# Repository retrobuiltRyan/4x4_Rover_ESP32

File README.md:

# 4x4_Rover_ESP32
Video is a great overview of capabilites and features.<br>

Generic platform for 1:10 scale robot rover (skid steer style) with ESP32 and PS4 controller.  Hardware [mostly] from scratch. The 1:10 scale (primarily wheel span and chassis width) mimics some common RC and toy-scale bodies. Makes a uniquie sleeper build that can share a body from off-the-shelf kids toys. PCB has enough functionality to expand into complex robots.

PCB can control up to 6 DC motors and 8 Servo Motors. 

## CAD Project (View only) Feel free remix!
[4x4 Rover CAD](https://cad.onshape.com/documents/4f9534eae9bdb33bcf172fe9/w/a4954ea2d6d5d21b33e1d9c4/e/6819e643c891bac21c58d472) (Make a free onShape account to copy and edit)

## 🔩 Mechanical Hardware/Fasteners for Assembly (BoM)
| Item | Assembly     | Description                                | Qty | Cost   | Line Total | Vendor Link / McMaster Part#         |
|------|--------------|--------------------------------------------|-----|--------|------------|--------------------------------------------------------------------------------------|
| 1    | Wheel        | Lego "Compatible" Tire 94x38 (or similar)  | 1   | $17.65 | $17.65     | [Link](https://www.aliexpress.us/item/3256808684598937.html)                         |
| 2    | Drive        | Shaft Coupler, 4mm dia                     | 4   | $1.65  | $6.60      | [Link](https://www.aliexpress.us/item/3256805863207590.html)                         |
| 3    | Drive        | Motor 12V, 82 RPM                          | 4   | $5.74  | $22.96     | [Link](https://www.aliexpress.us/item/3256807500148966.html) or [Link](https://www.aliexpress.us/item/3256807350691232.html)                       |
| alt3 | Drive        | Motor 12V, 82 RPM + RC Wheel               | 4   | $6.46  | $25.84     | [Link](https://www.aliexpress.us/item/3256806026937992.html)                         |
| 5    | Chassis      | #6-32 x 0.5 in Round Head Screw            | 28  | $0.03  | $0.94      | 90279A148                                                                            |
| 6    | Chassis      | #6-32 x 0.75 in Round Head Screw           | 20  | $0.04  | $0.83      | 90279A151                                                                            |
| 7    | Chassis      | #6-32 nut                                  | 20  | $0.02  | $0.40      | 90480A007                                                                            |
| 8    | Chassis      | #6-32 nylon lock nut                       | 20  | $0.04  | $0.80      | 99397A622                                                                            |
| 9    | Chassis      | #6-32 x 1.0 in F/F Hex Standoff (optional) | 4   | $0.47  | $1.88      | 90480A005                                                                            |
| 10   | Wheel        | #4-40 x 0.5 in Round Head Screw            | 16  | $0.02  | $0.32      | 90272A110                                                                            |
| 11   | Wheel        | #4-40 nut                                  | 16  | $0.01  | $0.16      | 90480A005                                                                            |
| 12   | Wheel        | #4-40 lock nut (optional)                  | 16  | $0.03  | $0.48      | 90631A005                                                                            |
| 13   | On/Off switch | Switch, SPST                              | 1   | $0.71  | $0.71      | [Link](https://www.digikey.com/en/products/detail/e-switch/RA11131121/2720267)       |
| 14   | 3D Print Parts| PLA Filament (or whatever)                | ~650g |$0.02/g | $13      | any                                                                                  | 
|      |              |                                            |     |        | **$66.74** | Alternate hardware not included in total cost                                        |

### Optional Forklift Assembly Motors + Parts. *Not a comprehensive list- just the essentials*
| Item | Assembly     | Description                                | Qty | Cost   | Line Total | Vendor Link / McMaster Part#         |
|------|--------------|--------------------------------------------|-----|--------|------------|--------------------------------------------------------------------------------------|
| 15   |Forklift      |Motor High Torque 12V, 50RPM, (37mm dia)    |  1  | $14    | $14        |   [Amazon](https://www.amazon.com/dp/B07K9KPDNV) or [AliExpress](https://www.aliexpress.us/item/2251832401105488.html)     |
|16    |Forklift      | Flange Coupler 6mm                         | 1    |$2     | $2         |  [AliExpress](https://www.aliexpress.us/item/3256805863207590.html?) |
| 17   |Forklift      |Motor (Linear Actuator ) 12V 50mm-stroke 15mm/s 64N        | 2   | $22    | $44        |    [AliExpress](https://www.aliexpress.us/item/3256808499012288.html)                           |
| 18   |Forklift      |Bearing 625ZZ , 16mm OD dia, (5x16x5mm)                    | 8   |$0.55   |$4.40       |[AliExpress](https://www.aliexpress.us/item/3256809469842556.html)                    |
| 19   |Forklift      |Bearing, 11mm OD dia, (5x11x5mm)                           | 10  | $0.25  | $2.50      | [AliExpress](https://www.aliexpress.us/item/3256807482131308.html)                   |                           

## 🪫 Electronics (Control and Drive PCB)
PS4 Controller (Renewed) https://www.amazon.com/dp/B07QD2HK7B/ref=dp_cr_wdg_tit_rfb  (subject to availability most of the time)
| Reference | Value | Qty | DigiKey P/N | Adafruit P/N | AliExpress | Line total Cost |
|------------|--------|-----|--------------|---------------|-------------|-----------------|
| BZ1 | Buzzer_5V | 1 | 445-2525-1-ND |  |  | 0.62 |
| C1,C3,C4,C5,C7,C8,C9 | 0.1uF 50V | 7 | 1276-1068-1-ND |  |  | 0.91 |
| C6,C10,C11 | 0.22uF 50V CER | 3 | 445-2283-1-ND |  |  | 0.78 |
| C12,C13,C14 | 22uF 50V | 3 | 399-11438-1-ND |  |  | 1.05 |
| D1,D5,D10,D11 | LED | 4 | 1080-1419-1-ND |  |  | 0.84 |
| D6,D7,D8,D9 | WS2812B | 4 |  | 3094 |  | 0.64 |
| D12 | SMF15A | 1 | SMF15A-E3-08CT-ND |  |  | 0.13 |
| J1 | PINHD_1x2_Male | 1 | S1012EC-40-ND |  |  | 0.43 |
| J2,J12,J14,J16 | Screw_Terminal_4_P3.50mm | 4 | 732-691243110004-ND |  |  | 8.28 |
| J3,J15 | ServoPort_04 | 2 | S1012EC-40-ND |  |  | 0.86 |
| J4,J5,J8,J13 | Screw_Terminal_2_P3.50mm | 4 | 732-2747-ND |  |  | 3.16 |
| J9 | Barrel_Jack | 1 | EJ508A-ND |  |  | 1.22 |
| J17 | PINHD_1x3_Male | 1 |  |  |  | 0 |
| Q1 | MOSFET P-CH 30V 25A TO252 | 1 | 785-1106-1-ND |  |  | 1.43 |
| Q2 | MMBT2222A | 1 | MMBT2222ATPMSCT-ND |  |  | 0.1 |
| Q3 | AO3400A | 1 | 785-1000-1-ND |  |  | 0.46 |
| R1,R2,R4,R7,R8,R9, R10,R13,R18,R22, R36,R37,R38 | 10K | 12 | 311-10.0KFRCT-ND |  |  | 0.14 |
| R3,R6 | 100 | 2 | 311-100FRCT-ND |  |  | 0.2 |
| R5,R19,R20,R32 | 1K | 4 | 311-1.00KFRCT-ND |  |  | 0.44 |
| R16 | 220 | 1 | 311-220FRCT-ND |  |  | 0.1 |
| R17,R21 | 330 | 2 | 311-330FRCT-ND |  |  | 0.22 |
| R33 | 100k | 1 | 311-100KFRCT-ND |  |  | 0.1 |
| RN1,RN2,RN3 | 220 array | 3 | CAY16-201J4LFCT-ND |  |  | 0.3 |
| U1 | INA260 | 1 | 296-47777-1-ND |  |  | 5.52 |
| U2 | ESP32 | 1 | 1965-ESP32-DEVKITC-32UE-ND |  |  | 10 |
| U3 | PCA9685PW | 1 | 568-11925-1-ND |  |  | 3.04 |
| U4,U6,U9 | DRV8833 | 3 |  |  | [Link](https://www.aliexpress.us/item/3256806096142480.html) | 5.23 |
| U5 | UCC27511ADBV | 1 | 296-49474-1-ND |  |  | 1.13 |
| U7 | L7812 | 1 | 296-44522-1-ND |  |  | 1.81 |
| U8 | IMU LSM6DS3TR-C | 1 |  | 4503 |  | 9.95 |
| U14 | MAX40200AUK | 1 | 175-MAX40203AUK+TCT-ND |  |  | 1.75 |
| U15 | L7805 | 1 | 497-7255-1-ND |  |  | 0.84 |
| U18,U19 | MP1584 Buck Module | 2 |  |  | [Link](https://www.aliexpress.us/item/3256806890547813.html) | 1.06 |
| - | PCB | 1 |  |  |  | 1 |
|  |  | |  |  | Total | **$63.74** |

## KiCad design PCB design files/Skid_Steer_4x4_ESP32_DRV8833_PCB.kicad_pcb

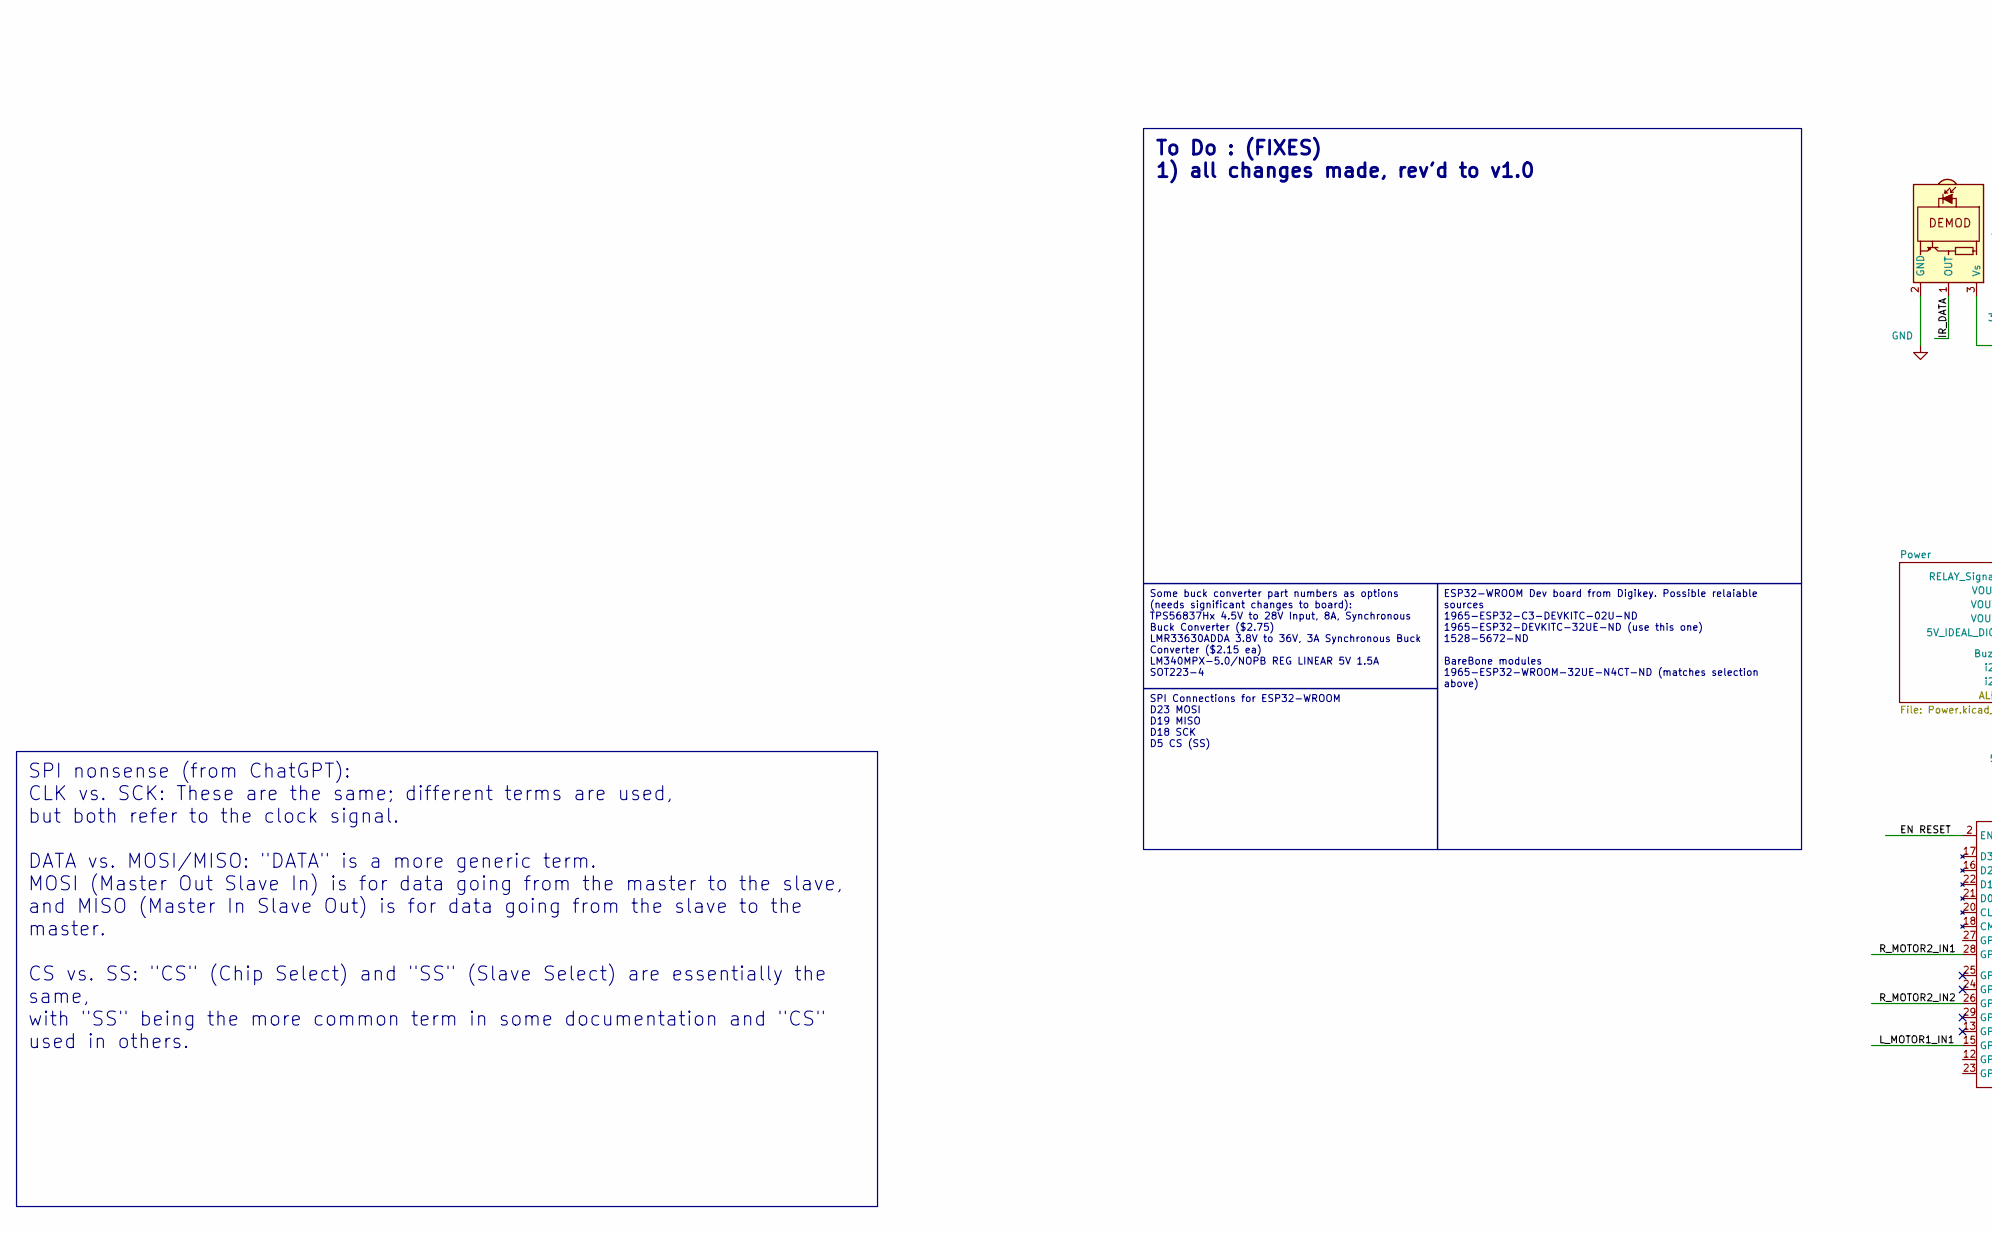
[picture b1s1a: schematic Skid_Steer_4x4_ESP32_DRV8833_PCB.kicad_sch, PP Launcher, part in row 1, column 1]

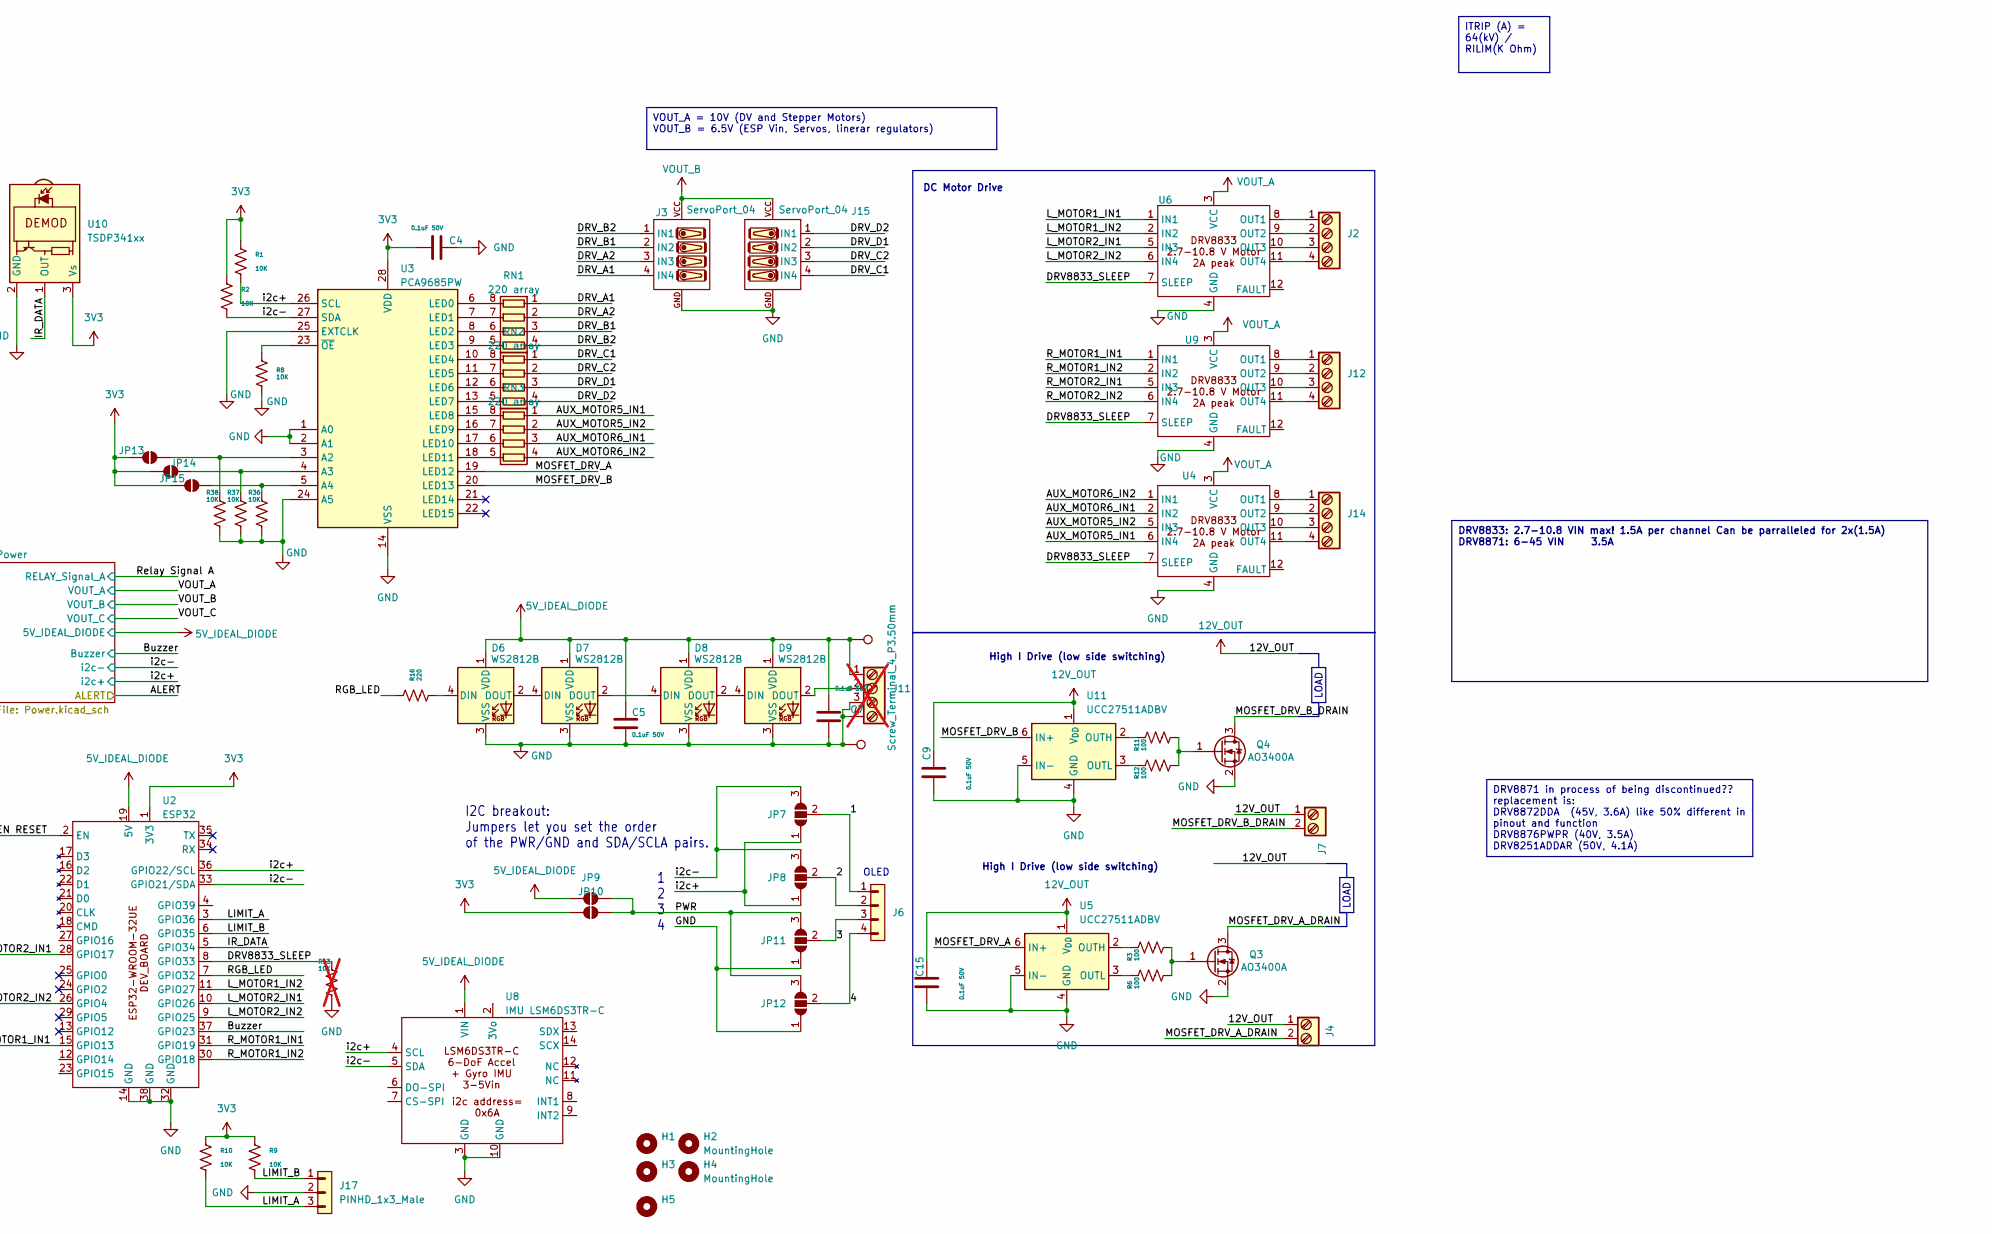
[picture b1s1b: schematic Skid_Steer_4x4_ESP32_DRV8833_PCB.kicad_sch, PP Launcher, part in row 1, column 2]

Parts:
C4, C5, C7, C9, C15: 0.1uF 50V; C_1206_3216Metric; DigiKey P/N 1276-1068-1-ND
D6, D7, D8, D9: WS2812B; LED_WS2812B_PLCC4_5.0x5.0mm_P3.2mm
H1, H2, H3, H4, H5: MountingHole; MountingHole_4.3mm_M4
J2, J12, J14: Screw_Terminal_4_P3.50mm; TerminalBlock_Phoenix_PT-1,5-4-3.5-H_1x04_P3.50mm_Horizontal; DigiKey P/N 732-691243110004-ND
J3, J15: ServoPort_04; ServoPort_04_Vertical; DigiKey P/N S1012EC-40-ND
J4, J7: Screw_Terminal_2_P3.50mm; TerminalBlock_Phoenix_PT-1,5-2-3.5-H_1x02_P3.50mm_Horizontal; DigiKey P/N 732-2747-ND
J6: PINHD_1x4_Male; PinHeader_1x04_P2.54mm_Vertical; DigiKey P/N S1012EC-40-ND
J11: Screw_Terminal_4_P3.50mm; TerminalBlock_Phoenix_PT-1,5-4-3.5-H_1x04_P3.50mm_Horizontal; not fitted
J17: PINHD_1x3_Male; PinHeader_1x03_P2.54mm_Vertical
JP7, JP8, JP11, JP12: SolderJumper_3_Open; SolderJumper-3_P1.3mm_Open_RoundedPad1.0x1.5mm
JP9, JP10, JP13, JP14, JP15: SolderJumper_2_Open; SolderJumper-2_P1.3mm_Open_TrianglePad1.0x1.5mm
Q3, Q4: AO3400A; SOT-23-3; DigiKey P/N 785-1000-1-ND
R1, R2, R8, R9, R10, R36, R37, R38: 10K; R_1206_3216Metric; DigiKey P/N 311-10.0KFRCT-ND
R3, R6, R11, R12: 100; R_1206_3216Metric; DigiKey P/N 311-100FRCT-ND
R13: 10K; R_1206_3216Metric; DigiKey P/N 311-10.0KFRCT-ND; not fitted
R16: 220; R_1206_3216Metric; DigiKey P/N 311-220FRCT-ND
RN1, RN2, RN3: 220 array; CAT16-4_R-Array_1206; DigiKey P/N CAY16-201J4LFCT-ND
TP4, TP5, TP6: TestPoint; TestPoint_Pad_1.5x1.5mm
U2: ESP32; ESP32-WROOM-32UE_DEV_BOARD; DigiKey P/N 1965-ESP32-DEVKITC-32UE-ND
U3: PCA9685PW; TSSOP-28_4.4x9.7mm_P0.65mm; DigiKey P/N 568-11925-1-ND
U4, U6, U9: DRV8833; DRV8833_aliexpress
U5, U11: UCC27511ADBV; SOT-23-6; DigiKey P/N 296-49474-1-ND
U8: IMU LSM6DS3TR-C; LSM6DS3TR-C_Adafruit
U10: TSDP341xx; Vishay_MOLD-3Pin

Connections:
3V3: C4.1, JP10.1 (A), JP13.1 (A), JP14.1 (A), JP15.1 (A), R1.2, R2.2, R9.2, R10.2, U2.1 (3V3), U3.28 (VDD), U10.3 (Vs); also elsewhere on the board
5V_IDEAL_DIODE: C5.1, C7.1, D6.1 (VDD), D7.1 (VDD), D8.1 (VDD), D9.1 (VDD), J11.1, JP9.1 (A), TP5.1, U2.19 (5V), U8.1 (VIN); also elsewhere on the board
12V_OUT: C9.2, C15.2, J4.1, J7.1, U5.1 (V_{DD}), U11.1 (V_{DD}); also elsewhere on the board
/1: J6.1, JP7.2 (C)
/2: J6.2, JP8.2 (C)
/3: J6.3, JP11.2 (C)
/4: J6.4, JP12.2 (C)
/AUX_MOTOR5_IN1: RN3.1 (R1.1), U4.6 (IN4)
/AUX_MOTOR5_IN2: RN3.2 (R2.1), U4.5 (IN3)
/AUX_MOTOR6_IN1: RN3.3 (R3.1), U4.2 (IN2)
/AUX_MOTOR6_IN2: RN3.4 (R4.1), U4.1 (IN1)
/Buzzer: U2.37 (GPIO23); also elsewhere on the board
/DRV8833_SLEEP: R13.1, U2.8 (GPIO33), U4.7 (SLEEP), U6.7 (SLEEP), U9.7 (SLEEP)
/DRV_A1: J3.4 (IN4), RN1.1 (R1.1)
/DRV_A2: J3.3 (IN3), RN1.2 (R2.1)
/DRV_B1: J3.2 (IN2), RN1.3 (R3.1)
/DRV_B2: J3.1 (IN1), RN1.4 (R4.1)
/DRV_C1: J15.4 (IN4), RN2.1 (R1.1)
/DRV_C2: J15.3 (IN3), RN2.2 (R2.1)
/DRV_D1: J15.2 (IN2), RN2.3 (R3.1)
/DRV_D2: J15.1 (IN1), RN2.4 (R4.1)
/EN RESET: U2.2 (EN)
/IR_DATA: U2.5 (GPIO34), U10.1 (OUT)
/LIMIT_A: J17.3, R10.1, U2.3 (GPIO36)
/LIMIT_B: J17.1, R9.1, U2.6 (GPIO35)
/L_MOTOR1_IN1: U2.15 (GPIO13), U6.1 (IN1)
/L_MOTOR1_IN2: U2.11 (GPIO27), U6.2 (IN2)
/L_MOTOR2_IN1: U2.10 (GPIO26), U6.5 (IN3)
/L_MOTOR2_IN2: U2.9 (GPIO25), U6.6 (IN4)
/MOSFET_DRV_A: U3.19 (LED12), U5.6 (IN+)
/MOSFET_DRV_A_DRAIN: J4.2, Q3.3 (D)
/MOSFET_DRV_B: U3.20 (LED13), U11.6 (IN+)
/MOSFET_DRV_B_DRAIN: J7.2, Q4.3 (D)
/PWR: JP9.2 (B), JP10.2 (B), JP11.3 (B), JP12.3 (B)
/RGB_LED: R16.2, U2.7 (GPIO32)
/R_MOTOR1_IN1: U2.31 (GPIO19), U9.1 (IN1)
/R_MOTOR1_IN2: U2.30 (GPIO18), U9.2 (IN2)
/R_MOTOR2_IN1: U2.28 (GPIO17), U9.5 (IN3)
/R_MOTOR2_IN2: U2.26 (GPIO4), U9.6 (IN4)
/i2c+: JP7.1 (A), JP8.1 (A), R1.1, U2.36 (GPIO22/SCL), U3.26 (SCL), U8.4 (SCL); also elsewhere on the board
/i2c-: JP7.3 (B), JP8.3 (B), R2.1, U2.33 (GPIO21/SDA), U3.27 (SDA), U8.5 (SDA); also elsewhere on the board
GND: C4.2, C5.2, C7.2, C9.1, C15.1, D6.3 (VSS), D7.3 (VSS), D8.3 (VSS), D9.3 (VSS), J3.GND, J11.3, J11.4, J15.GND, J17.2, JP11.1 (A), JP12.1 (A), Q3.2 (S), Q4.2 (S), R8.2, R13.2, R36.2, R37.2, R38.2, TP6.1, U2.14 (GND), U2.32 (GND), U2.38 (GND), U3.1 (A0), U3.2 (A1), U3.14 (VSS), U3.24 (A5), U3.25 (EXTCLK), U4.4 (GND), U5.4 (GND), U5.5 (IN-), U6.4 (GND), U8.3 (GND), U8.10 (GND), U9.4 (GND), U10.2 (GND), U11.4 (GND), U11.5 (IN-); also elsewhere on the board
unnamed: D6.4 (DIN), R16.1
unnamed: D6.2 (DOUT), D7.4 (DIN)
unnamed: D7.2 (DOUT), D8.4 (DIN)
unnamed: D8.2 (DOUT), D9.4 (DIN)
unnamed: D9.2 (DOUT), J11.2, TP4.1
unnamed: JP13.2 (B), R38.1, U3.3 (A2)
unnamed: JP14.2 (B), R37.1, U3.4 (A3)
unnamed: JP15.2 (B), R36.1, U3.5 (A4)
unnamed: Q3.1 (G), R3.2, R6.2
unnamed: Q4.1 (G), R11.2, R12.2
unnamed: RN1.8 (R1.2), U3.6 (LED0)
unnamed: RN1.7 (R2.2), U3.7 (LED1)
unnamed: RN1.6 (R3.2), U3.8 (LED2)
unnamed: RN1.5 (R4.2), U3.9 (LED3)
unnamed: RN2.8 (R1.2), U3.10 (LED4)
unnamed: RN2.7 (R2.2), U3.11 (LED5)
unnamed: RN2.6 (R3.2), U3.12 (LED6)
unnamed: RN2.5 (R4.2), U3.13 (LED7)
unnamed: RN3.8 (R1.2), U3.15 (LED8)
unnamed: RN3.7 (R2.2), U3.16 (LED9)
unnamed: RN3.6 (R3.2), U3.17 (LED10)
unnamed: RN3.5 (R4.2), U3.18 (LED11)
unnamed: R8.1, U3.23 (~OE)
unnamed: J14.1, U4.8 (OUT1)
unnamed: J14.2, U4.9 (OUT2)
unnamed: J14.3, U4.10 (OUT3)
unnamed: J14.4, U4.11 (OUT4)
unnamed: R3.1, U5.2 (OUTH)
unnamed: R6.1, U5.3 (OUTL)
unnamed: J2.1, U6.8 (OUT1)
unnamed: J2.2, U6.9 (OUT2)
unnamed: J2.3, U6.10 (OUT3)
unnamed: J2.4, U6.11 (OUT4)
unnamed: J12.1, U9.8 (OUT1)
unnamed: J12.2, U9.9 (OUT2)
unnamed: J12.3, U9.10 (OUT3)
unnamed: J12.4, U9.11 (OUT4)
unnamed: R11.1, U11.2 (OUTH)
unnamed: R12.1, U11.3 (OUTL)
VOUT_A: U4.3 (VCC), U6.3 (VCC), U9.3 (VCC); also elsewhere on the board
VOUT_B: J3.VCC, J15.VCC; also elsewhere on the board

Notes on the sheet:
VOUT_A = 10V (DV and Stepper Motors) VOUT_B = 6.5V (ESP Vin, Servos, linerar regulators)
LOAD
SPI Connections for ESP32-WROOM D23 MOSI D19 MISO D18 SCK D5 CS (SS)
SPI nonsense (from ChatGPT): CLK vs. SCK: These are the same; different terms are used, but both refer to the clock signal. DATA vs. MOSI/MISO: "DATA" is a more generic term. MOSI (Master Out Slave In) is for data going from the master to the slave, and MISO (Master In Slave Out) is for data going 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
Some buck converter part numbers as options (needs significant changes to board): TPS56837Hx 4.5V to 28V Input, 8A, Synchronous Buck Converter ($2.75) LMR33630ADDA 3.8V to 36V, 3A Synchronous Buck Converter ($2.15 ea) LM340MPX-5.0/NOPB REG LINEAR 5V 1.5A SOT223-4
To Do : (FIXES) 1) all changes made, rev'd to v1.0
ITRIP (A) = 64(kV) / RILIM(K Ohm)
ESP32-WROOM Dev board from Digikey. Possible relaiable sources 1965-ESP32-C3-DEVKITC-02U-ND 1965-ESP32-DEVKITC-32UE-ND (use this one) 1528-5672-ND BareBone modules 1965-ESP32-WROOM-32UE-N4CT-ND (matches selection above)
DRV8871 in process of being discontinued?? replacement is: DRV8872DDA (45V, 3.6A) like 50% different in pinout and function DRV8876PWPR (40V, 3.5A) DRV8251ADDAR (50V, 4.1A)
DRV8833: 2.7-10.8 VIN max! 1.5A per channel Can be parralleled for 2x(1.5A) DRV8871: 6-45 VIN 3.5A
DC Motor Drive
1 2 3 4
I2C breakout: Jumpers let you set the order of the PWR/GND and SDA/SCLA pairs.
High I Drive (low side switching)
OLED

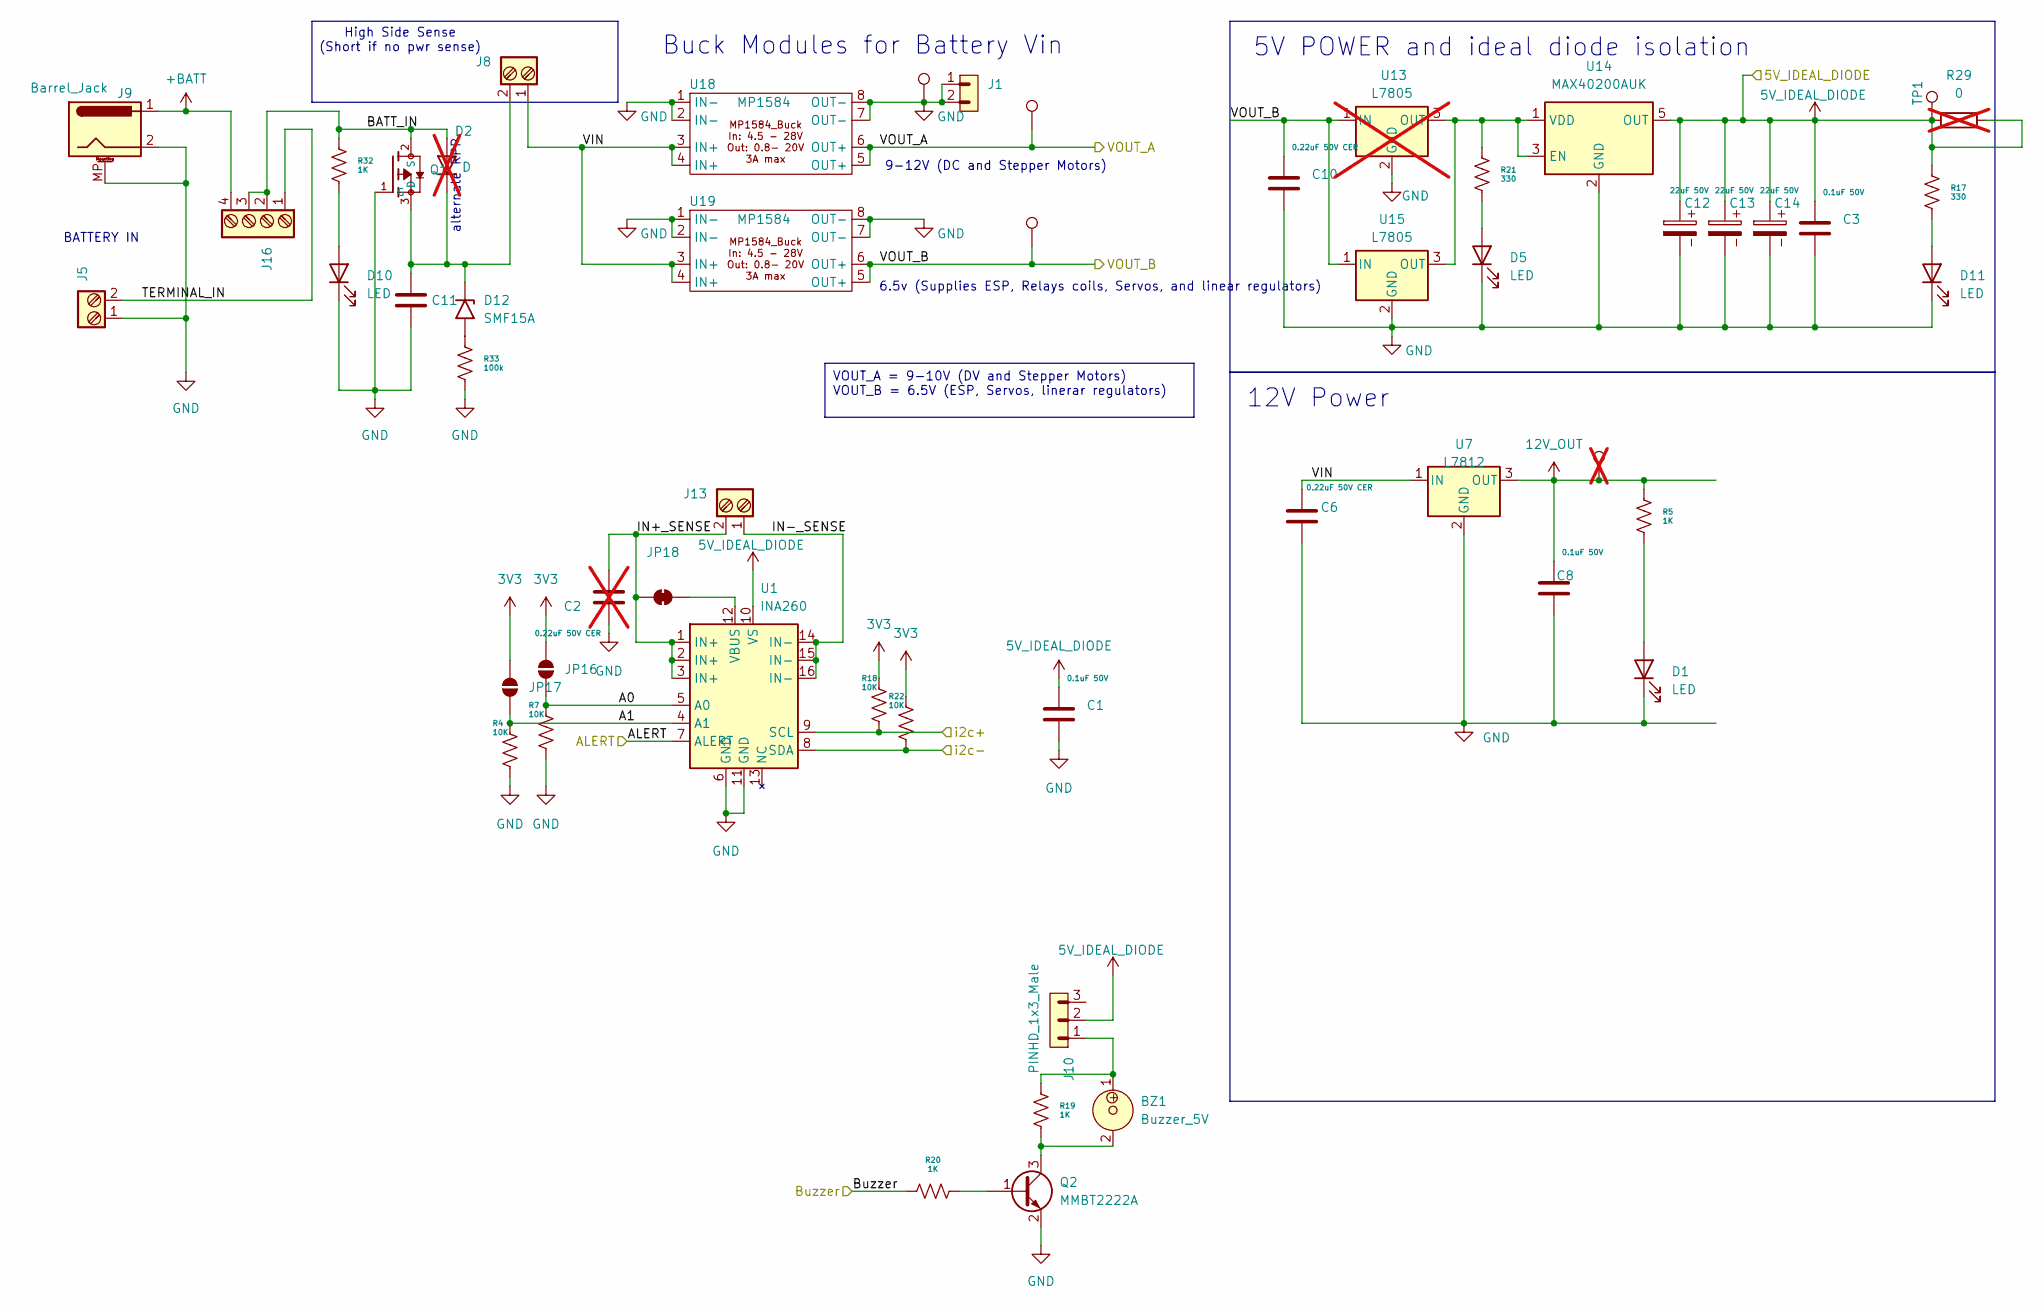
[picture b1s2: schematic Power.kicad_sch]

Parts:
BZ1: Buzzer_5V; MagneticBuzzer_ProSignal_ABT-410-RC; DigiKey P/N 445-2525-1-ND
C1, C3, C8: 0.1uF 50V; C_1206_3216Metric; DigiKey P/N 1276-1068-1-ND
C2: 0.22uF 50V CER; C_1206_3216Metric; DigiKey P/N 445-2283-1-ND; not fitted
C6, C10, C11: 0.22uF 50V CER; C_1206_3216Metric; DigiKey P/N 445-2283-1-ND
C12, C13, C14: 22uF 50V; CP_Elec_5x5.3; DigiKey P/N 399-11438-1-ND
D1, D5, D10, D11: LED; LED_1206_3216Metric; DigiKey P/N 1080-1419-1-ND
D2: D; D_SMC_Handsoldering; DigiKey P/N S5AC-FDICT-ND; not fitted
D12: SMF15A; D_SMF; DigiKey P/N SMF15A-E3-08CT-ND
J1: PINHD_1x2_Male; PinHeader_1x02_P2.54mm_Vertical; DigiKey P/N S1012EC-40-ND
J5, J8, J13: Screw_Terminal_2_P3.50mm; TerminalBlock_Phoenix_PT-1,5-2-3.5-H_1x02_P3.50mm_Horizontal; DigiKey P/N 732-2747-ND
J9: Barrel_Jack; BarrelJack_GCT_DCJ200-10-A_Horizontal; DigiKey P/N EJ508A-ND
J10: PINHD_1x3_Male; PinHeader_1x03_P2.54mm_Vertical; DigiKey P/N S1012EC-40-ND
J16: Screw_Terminal_4_P3.50mm; TerminalBlock_Phoenix_PT-1,5-4-3.5-H_1x04_P3.50mm_Horizontal; DigiKey P/N 732-691243110004-ND
JP16, JP17: SolderJumper_2_Open; SolderJumper-2_P1.3mm_Open_TrianglePad1.0x1.5mm
JP18: SolderJumper_2_Bridged; SolderJumper-2_P1.3mm_Bridged_RoundedPad1.0x1.5mm
Q1: MOSFET P-CH 30V 25A TO252; MOSFET_P-CH_30V_25A_TO252; DigiKey P/N 785-1106-1-ND
Q2: MMBT2222A; SOT-23; DigiKey P/N MMBT2222ATPMSCT-ND
R4, R7, R18, R22: 10K; R_1206_3216Metric; DigiKey P/N 311-10.0KFRCT-ND
R5, R19, R20, R32: 1K; R_1206_3216Metric; DigiKey P/N 311-1.00KFRCT-ND
R17, R21: 330; R_1206_3216Metric; DigiKey P/N 311-330FRCT-ND
R29: 0; R_2512_6332Metric_Pad1.40x3.35mm_HandSolder; DigiKey P/N YAG1232CT-ND; not fitted
R33: 100k; R_1206_3216Metric; DigiKey P/N 311-100KFRCT-ND
TP1: TestPoint; TestPoint_Pad_2.0x2.0mm
TP2: uC +5V; TestPoint_Pad_2.0x2.0mm; not fitted
TP10, TP11, TP12: TestPoint; TestPoint_Pad_1.5x1.5mm
U1: INA260; TSSOP-16_4.4x5mm_P0.65mm; DigiKey P/N 296-47777-1-ND
U7: L7812; TO-263-3_TabPin2; DigiKey P/N 296-44522-1-ND
U13: L7805; TO-220-3_Vertical; not fitted
U14: MAX40200AUK; SOT-23-5; DigiKey P/N 175-MAX40203AUK+TCT-ND
U15: L7805; TO-252-2; DigiKey P/N 497-7255-1-ND
U18, U19: MP1584

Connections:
3V3: JP16.2 (B), JP17.2 (B), R18.1, R22.1; also elsewhere on the board
5V_IDEAL_DIODE: C1.1, C3.1, C12.1, C13.1, C14.1, J10.2, R17.1, R29.1, R29.2, TP1.1, U1.10 (VS), U14.5 (OUT); also elsewhere on the board
12V_OUT: C8.1, R5.2, TP2.1, U7.3 (OUT); also elsewhere on the board
+BATT: J9.1, J16.4
/Buzzer: R20.1; also elsewhere on the board
/Power/A0: JP16.1 (A), R7.1, U1.5 (A0)
/Power/A1: JP17.1 (A), R4.1, U1.4 (A1)
/Power/ALERT: U1.7 (ALERT)
/Power/BATT_IN: D2.2 (A), J16.2, J16.3, Q1.2 (S), R32.1
/Power/IN+_SENSE: C2.2, J13.2, JP18.1 (A), U1.1 (IN+), U1.2 (IN+), U1.3 (IN+)
/Power/IN-_SENSE: J13.1, U1.14 (IN-), U1.15 (IN-), U1.16 (IN-)
/Power/TERMINAL_IN: J5.2, J16.1
/Power/VIN: C6.1, J8.1, U7.1 (IN), U18.3 (IN+), U18.4 (IN+), U19.3 (IN+), U19.4 (IN+)
/i2c+: R18.2, U1.9 (SCL); also elsewhere on the board
/i2c-: R22.2, U1.8 (SDA); also elsewhere on the board
GND: C1.2, C2.1, C3.2, C6.2, C8.2, C10.2, C11.2, C12.2, C13.2, C14.2, D1.1 (K), D5.1 (K), D10.1 (K), D11.1 (K), J1.1, J1.2, J5.1, J9.2, J9.MP (MountPin), Q1.1 (G), Q2.2 (E), R4.2, R7.2, R33.2, TP12.1, U1.6 (GND), U1.11 (GND), U7.2 (GND), U13.2 (GND), U14.2 (GND), U15.2 (GND), U18.1 (IN-), U18.2 (IN-), U18.7 (OUT-), U18.8 (OUT-), U19.1 (IN-), U19.2 (IN-), U19.7 (OUT-), U19.8 (OUT-); also elsewhere on the board
unnamed: BZ1.1, J10.1, R19.1
unnamed: D1.2 (A), R5.1
unnamed: D5.2 (A), R21.2
unnamed: D10.2 (A), R32.2
unnamed: D11.2 (A), R17.2
unnamed: C11.1, D2.1 (K), D12.1 (A1), J8.2, Q1.3 (D)
unnamed: D12.2 (A2), R33.1
unnamed: JP18.2 (B), U1.12 (VBUS)
unnamed: Q2.1 (B), R20.2
unnamed: BZ1.2, Q2.3 (C), R19.2
unnamed: R21.1, U13.3 (OUT), U14.1 (VDD), U14.3 (EN), U15.3 (OUT)
VOUT_A: TP10.1, U18.5 (OUT+), U18.6 (OUT+); also elsewhere on the board
VOUT_B: C10.1, TP11.1, U13.1 (IN), U15.1 (IN), U19.5 (OUT+), U19.6 (OUT+); also elsewhere on the board

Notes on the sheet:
VOUT_A = 9-10V (DV and Stepper Motors) VOUT_B = 6.5V (ESP, Servos, linerar regulators)
12V Power
5V POWER and ideal diode isolation
6.5v (Supplies ESP, Relays coils, Servos, and linear regulators)
9-12V (DC and Stepper Motors)
alternate RPP
BATTERY IN
High Side Sense (Short if no pwr sense)
Buck Modules for Battery Vin

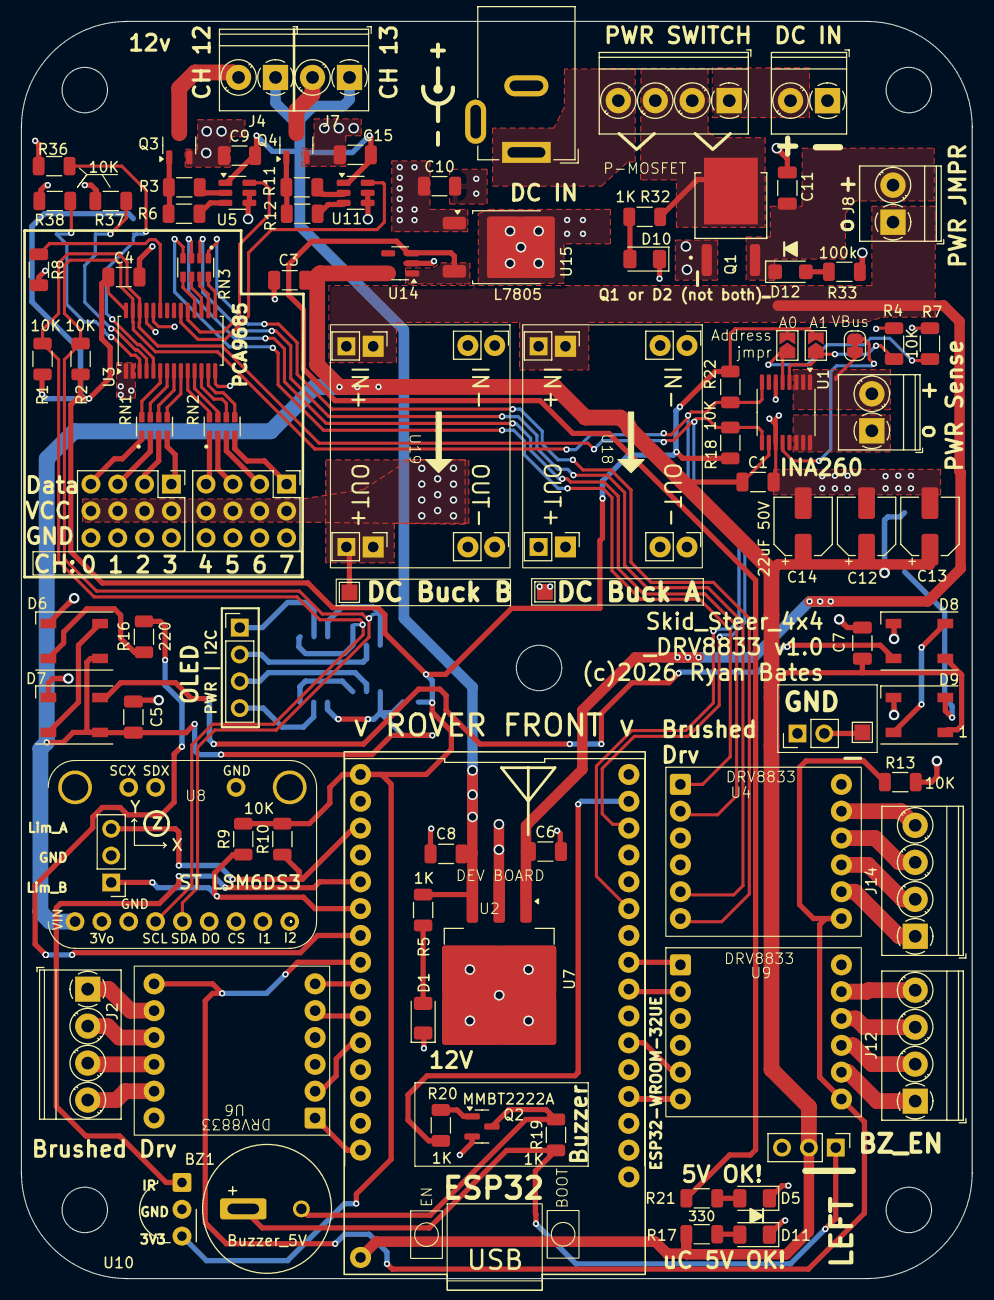
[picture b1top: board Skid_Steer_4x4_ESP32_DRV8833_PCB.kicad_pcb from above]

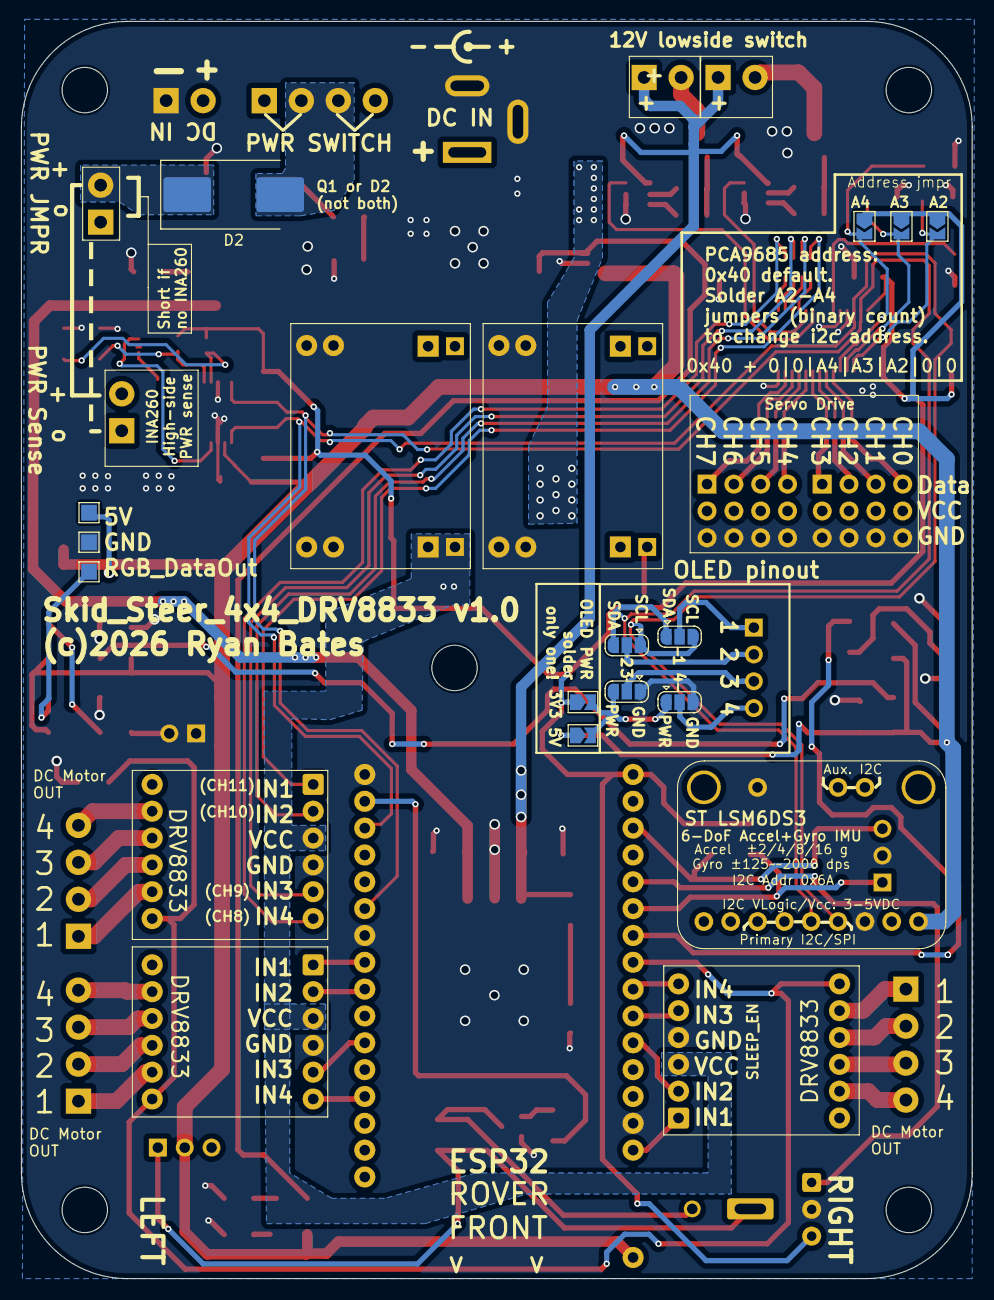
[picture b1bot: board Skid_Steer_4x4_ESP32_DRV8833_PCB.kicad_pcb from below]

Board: 2 copper layers, 90.0 x 119.0 mm, 111 parts (13 on the bottom side), 101 nets.

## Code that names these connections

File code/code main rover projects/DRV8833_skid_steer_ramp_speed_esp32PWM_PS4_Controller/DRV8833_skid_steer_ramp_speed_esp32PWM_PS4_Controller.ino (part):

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#include <esp_bt.h> // Include for BT MAC address

int driveDirection = 1;   // 1 = normal, -1 = reversed (drive direction/orientation mode)
#define BUZZER_PIN 23     // piezo buzzer
#define BUZZER_CHANNEL 8   // free LEDC channel (0–15 available, motors already use 0–7)

// Deadzone for joystick
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// bool lowSpeedMode = false;     // toggle state

// Motor driver pin assignments (DRV8833)
#define L_MOTOR1_IN1 13   //(Front Left) //was GPIO14, which was a strapping pin :(
#define L_MOTOR1_IN2 27   //(Front Left) 
#define L_MOTOR2_IN1 26   //(Rear Left)  
#define L_MOTOR2_IN2 25   //(Rear Left)  

#define R_MOTOR1_IN1 19   //(Front Right) 
#define R_MOTOR1_IN2 18   //(Front Right) 
#define R_MOTOR2_IN1 17    //(Rear Right)  //was GPIO5, which was a strapping pin :(
#define R_MOTOR2_IN2 4    //(Rear Right)

#define SLEEP_PIN 33      // DRV8833 nSLEEP pin

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  digitalWrite(SLEEP_PIN, LOW);  // Start with motor drive disabled

ledcSetup(BUZZER_CHANNEL, 2000, 8);   // 2 kHz, 8-bit resolution
ledcAttachPin(BUZZER_PIN, BUZZER_CHANNEL);

  Serial.begin(115200);
  delay(500);
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  ledcSetup(CH_R4, PWM_FREQ, PWM_RES);

  // Attach channels to pins
  ledcAttachPin(L_MOTOR1_IN1, CH_L1);
  ledcAttachPin(L_MOTOR1_IN2, CH_L2);
  ledcAttachPin(L_MOTOR2_IN1, CH_L3);
  ledcAttachPin(L_MOTOR2_IN2, CH_L4);

  ledcAttachPin(R_MOTOR1_IN1, CH_R1);
  ledcAttachPin(R_MOTOR1_IN2, CH_R2);
  ledcAttachPin(R_MOTOR2_IN1, CH_R3);
  ledcAttachPin(R_MOTOR2_IN2, CH_R4);

  // Sleep pin
  pinMode(SLEEP_PIN, OUTPUT);
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
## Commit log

2025-11-04 Create LICENSE
2025-12-20 Update vendor link for Motor 12V, 82 RPM
    Added an alternative vendor link for the 12V motor.
2026-01-09 Add PLA Filament cost to hardware list
2026-01-11 Revise electronics BoM with cost details
    Updated the electronics Bill of Materials (BoM) to include line total costs and a total cost summary.
2026-01-11 Update README with PCB features and cost adjustments
    Added details about PCB capabilities and updated total costs.
2026-01-11 Enhance README with GIF and PCB details
    Added GIF and expanded description of PCB functionality.
2026-01-12 Enhance README with CAD link and images
    Updated README to include CAD project link and additional images.
2026-01-12 Update CAD project link with account info
    Added note about creating a free onShape account for exporting and downloading the CAD project.
2026-01-12 Add linear actuator link to README
    Added a link for the linear actuator used in the forklift build.
2026-01-13 Add optional forklift assembly motors and parts list
2026-01-13 Fix formatting of resistor list in README.md
2026-01-14 Revise optional forklift assembly parts list
    Updated the list of optional forklift assembly motors and parts, including new items and adjustments to existing entries.
2026-01-15 Update CAD project description for clarity
2026-01-15 kiCAD files
2026-01-16 Add video link to README for project overview
    Added a video link for an overview of capabilities and features.

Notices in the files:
PCB design files/Skid_Steer_4x4_ESP32_DRV8833_PCB.kicad_pcb:
(c)2026 Ryan Bates
